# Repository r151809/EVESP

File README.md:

# EVESP
ESP32 (Lolin32) based EV charge controller
Implement charging controller according to SAE J1772 (https://en.wikipedia.org/wiki/SAE_J1772) and relay driver.

Project maturity: just schematics (no testing nor SW yet)!

Only fixed cables are supported (no PP support).

Recidual current (AC+DC) protection is planned with https://deltrixchargers.com/wp-content/uploads/2019/10/WA-DS-015-RCM14-03-Rev-B.pdf
https://www.stegen.com/nl/ev-producten/126-residual-current-sensor.html

Three relays, one for each phase. This is inteded for cases when there is unsymmetrical load in the house, and you still want to charge the car (maybe there is another car charging in one phase already). Another usecase is cars that go to sleep when not charged, and while sleeping they do not accept pre heat commands from the cloud. My take for that would be charging with single phase with 6A current, instead of not charging at all, full 3-phase charging only when you really want to charge. Changing the phases on the fly might not be supported by cars, but that is easy to overcome by stopping the charge before switching on/off any phases.

Misc features:
4 local LEDs
8 IO for external LEDs or buttons
1 up to 12 V LED output for lighting up the charging cable dummy socket (where you keep the cable when it's not connected to car)  

Many ideas (component selection) of the schematic are taken from https://github.com/SmartEVSE/smartevse and from http://www.analogevse.xyz/AnalogEVSE-en.html. 

PWM generation and Wifi connectivity is handled with LoLin32-board:
https://wiki.wemos.cc/products:lolin32:lolin32
It's discontinued already, but you can still find them from ebay.
Pinout is here: https://arduino-projekte.info/wemos-lolin32/

Security:
SW cannot enable relay drivers unless RCM is happy and CP is connected to some load. So the design should be safe in case of forced disconnect and any ground leakage.

Manufacturing of the first PCB patch was done by Itead.cc with files in EVESP.zip.

## Copying
Feel free to copy anything I have added to this project. If it is not too much to ask, please let me know what you are doing (it's not mandatory) :). Also any bug's would be nice to know.

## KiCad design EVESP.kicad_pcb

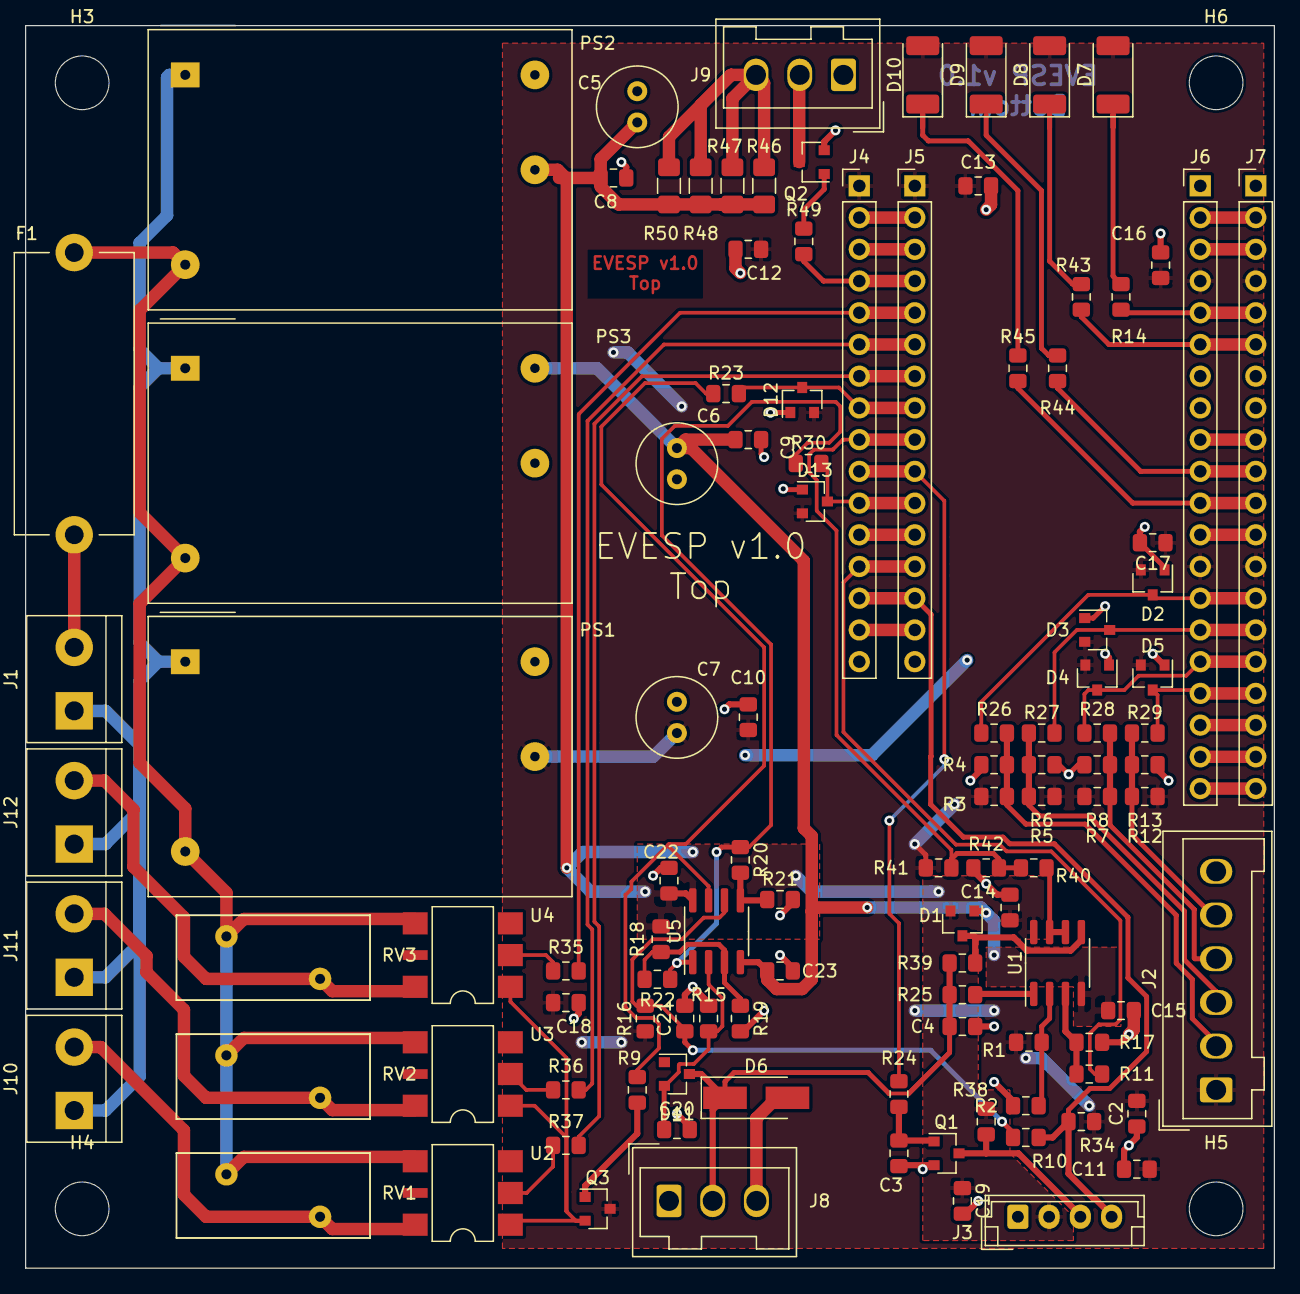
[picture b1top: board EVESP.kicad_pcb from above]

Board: 2 copper layers, 100.0 x 99.5 mm, 113 parts (0 on the bottom side), 68 nets.

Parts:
C2, C12: 10u; C_0805_2012Metric_Pad1.15x1.40mm_HandSolder
C3: DNI 100n; R_0805_2012Metric_Pad1.15x1.40mm_HandSolder
C4: 270p; C_0805_2012Metric_Pad1.15x1.40mm_HandSolder
C5, C6, C7: 47u; C_Radial_D6.3mm_H11.0mm_P2.50mm
C8, C9, C10, C11, C13, C14, C15, C16, C17, C18, C19, C20, C21, C22, C23: 100n; C_0805_2012Metric_Pad1.15x1.40mm_HandSolder
D1, D2, D3, D4, D5, D11, D12, D13: BAT54S; SOT-23
D6: SMAJ13CA-13-F; D_SMA_Handsoldering
D7, D8, D9, D10: LED; LED_2010_5025Metric_Pad1.52x2.65mm_HandSolder
F1: 1.25A; Fuseholder_Cylinder-5x20mm_Stelvio-Kontek_PTF78_Horizontal_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
H3, H4, H5, H6: MountingHole; MountingHole_4.3mm_M4
J1, J10, J11, J12: Screw_Terminal_01x02; TerminalBlock_bornier-2_P5.08mm
J2: Screw_Terminal_01x06; Wago_734-136_1x06_P3.50mm_Vertical
J3: Conn_01x04; JST_EH_B4B-EH-A_1x04_P2.50mm_Vertical
J4: Conn_01x16_Male; PinHeader_1x16_P2.54mm_Vertical
J5: Conn_01x16_Female; PinHeader_1x16_P2.54mm_Vertical
J6: Conn_01x20_Female; PinHeader_1x20_P2.54mm_Vertical
J7: Conn_01x20_Male; PinHeader_1x20_P2.54mm_Vertical
J8, J9: Screw_Terminal_01x03; Wago_734-133_1x03_P3.50mm_Vertical
PS1: IRM-02-3.3; Converter_ACDC_MeanWell_IRM-02-xx_THT
PS2, PS3: IRM-02-12; Converter_ACDC_MeanWell_IRM-02-xx_THT
Q1, Q2, Q3: BC847; SOT-23
R1, R2, R3, R4, R5, R6, R7, R8, R9, R10, R11, R12, R13, R16, R19, R20, R24, R34, R38, R39, R41, R42, R49: 10k; R_0805_2012Metric_Pad1.15x1.40mm_HandSolder
R14, R25, R43, R44, R45: 1k; R_0805_2012Metric_Pad1.15x1.40mm_HandSolder
R15, R22: 1M; R_0805_2012Metric_Pad1.15x1.40mm_HandSolder
R17, R23, R30: 100k; R_0805_2012Metric_Pad1.15x1.40mm_HandSolder
R18: 6k8; R_0805_2012Metric_Pad1.15x1.40mm_HandSolder
R21, R40: 47k; R_0805_2012Metric_Pad1.15x1.40mm_HandSolder
R26, R27, R28, R29, R35, R36, R37: 470R; R_0805_2012Metric_Pad1.15x1.40mm_HandSolder
R46, R47, R48, R50: 470R; R_1206_3216Metric_Pad1.42x1.75mm_HandSolder
RV1, RV2, RV3: V275LA20AP; RV_Disc_D15.5mm_W6.8mm_P7.5mm
U1, U5: LM7332; SOIC-8_3.9x4.9mm_P1.27mm
U2, U3, U4: MOC3063M; SMDIP-6_W7.62mm

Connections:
+3V3: C2.2, C7.1, C10.1, C11.1, C12.1, C13.1, C16.1, C17.1, C18.1, D2.2, D3.2, D4.2, D5.2, D7.2, D8.2, D9.2, D10.2, D12.2, D13.2, J2.1, J4.1, J5.1, J6.4, J6.13, J7.4, J7.13, PS1.4, Q3.3, R1.2, R3.1, R5.1, R7.1, R12.1, R16.1, R34.1, R41.1
+12V: C5.1, C8.1, C14.1, C19.1, C22.1, D1.2, J3.2, PS2.4, R18.1, R38.1, R46.1, R47.1, R48.1, R50.1, U1.8, U5.8
-12V: C6.2, C9.2, C15.2, C23.2, D1.1, PS3.3, U1.4, U5.4
/CP: C4.1, D6.1, D11.3, J8.2, R25.1, R39.2
/CP_in: J4.9, J5.9, R40.1, R41.2, R42.1
/CP_out: J4.13, J5.13, R11.2
/Charge: R20.1, R22.1, R30.1, U5.1
/D0: D2.3, J6.14, J7.14, R26.2
/D1: D3.3, J6.15, J7.15, R27.2
/D2: D4.3, J6.16, J7.16, R28.2
/D3: D5.3, J6.17, J7.17, R29.2
/L1: F1.1, J1.2
/L1_fused: F1.2, PS1.2, PS2.2, PS3.2, RV1.2, RV2.2, RV3.2, U2.4, U3.4, U4.4
/LED0_n: J6.11, J7.11, R45.2
/LED1_n: J6.10, J7.10, R44.2
/LED2_n: J6.6, J7.6, R43.2
/LED3_n: J6.5, J7.5, R14.2
/Light_n: J4.4, J5.4, R49.2
/N: J1.1, J10.1, J11.1, J12.1, PS1.1, PS2.1, PS3.1
/RCM_fail: J3.4, J4.14, J5.14, R10.1, R34.2
/RCM_test: J3.3, Q1.3, R38.2
/RCM_test_n: J4.10, J5.10, R24.1
/REL_0: J10.2, RV1.1, U2.6
/REL_1: J11.2, RV2.1, U3.6
/REL_2: J12.2, RV3.1, U4.6
/Relay_0_n: J4.5, J5.5, R35.2
/Relay_1_n: J4.6, J5.6, R36.2
/Relay_2_n: J4.7, J5.7, R37.2
/SafeToCharge: R9.1, R23.1, U5.7
GND: C2.1, C3.2, C4.2, C5.2, C6.1, C7.2, C8.2, C9.1, C10.2, C11.2, C12.2, C13.2, C14.2, C15.1, C16.2, C17.2, C18.2, C19.2, C20.2, C21.2, C22.2, C23.1, D2.1, D3.1, D4.1, D5.1, D6.2, D12.1, D13.1, J2.6, J3.1, J4.16, J5.16, J6.1, J6.7, J6.8, J6.18, J7.1, J7.7, J7.8, J7.18, J8.1, J8.3, J9.1, PS1.3, PS2.3, PS3.4, Q1.2, Q2.2, R2.1, R4.2, R6.2, R8.2, R13.2, R15.2, R17.1, R19.2, R21.2, R42.2
unnamed: C3.1, Q1.1, R24.2
unnamed: C20.1, D11.2, R15.1, U5.2
unnamed: C21.1, R10.2, R16.2, U5.6
unnamed: D1.3, R39.1, U1.5
unnamed: D7.1, R14.1
unnamed: D8.1, R43.1
unnamed: D9.1, R44.1
unnamed: D10.1, R45.1
unnamed: D12.3, J4.8, J5.8, R23.2
unnamed: D13.3, J4.11, J5.11, R30.2
unnamed: J2.2, R3.2, R4.1, R26.1
unnamed: J2.3, R5.2, R6.1, R27.1
unnamed: J2.4, R7.2, R8.1, R28.1
unnamed: J2.5, R12.2, R13.1, R29.1
unnamed: J4.2, J5.2
unnamed: J4.3, J5.3
unnamed: J4.12, J5.12
unnamed: J4.15, J5.15
unnamed: J6.2, J7.2
unnamed: J6.3, J7.3
unnamed: J6.9, J7.9
unnamed: J6.12, J7.12
unnamed: J6.19, J7.19
unnamed: J6.20, J7.20
unnamed: J9.2, Q2.3
unnamed: J9.3, R46.2, R47.2, R48.2, R50.2
unnamed: Q2.1, R49.1
unnamed: Q3.1, R9.2
unnamed: Q3.2, U2.1, U3.1, U4.1
unnamed: R1.1, R2.2, U1.2
unnamed: R11.1, R17.2, U1.3
unnamed: R18.2, R19.1, R22.2, U5.3
unnamed: R20.2, R21.1, U5.5
unnamed: R25.2, U1.1
unnamed: R35.1, U4.2
unnamed: R36.1, U3.2
unnamed: R37.1, U2.2
unnamed: R40.2, U1.6, U1.7

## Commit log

2020-02-27 Initial version.
2020-02-27 Added PDF of the schematics.
2020-02-27 Update README.md
    Wrote initial info.
2020-02-29 Only 4 external LEDs. Smaller layout.
2020-02-29 Added analog protection against disconnect and diode failure on car side.
2020-02-29 pdf plot
2020-03-01 Added HW safety. No relay drive unless the CP is connected and RCM is happy.
2020-03-01 +12V connectivity fixed
2020-03-01 Layout shrink to <= 10cm x 10 cm
2020-03-01 Added edge prints. Added prints.
2020-03-01 Better +3V3 plane.
2020-03-01 Minor changes.
2020-03-01 PDF update.
2020-03-01 AC side changed for 2mm clearance.
2020-03-01 Added hysteresis to charge -signal. Schematic review changes fixed.
2020-03-01 Layout ready. PDF updated.
2020-03-01 Added gerber and drill files.
2020-03-02 Fixed +-12V drive towards the ESP32 (added resistor and a diode).
2020-03-02 Gerbers generated: Fixed +-12V drive towards the ESP32 (added resistor and a diode).
2020-03-02 Added single drill file with PTH's and NPTH's
2020-03-02 Board cutting fine tuned to leave more clearance on right side connector before edge cut.. Added final production files as zip.
2020-03-12 C2 decal name fixed (both work fine so just a style fix)
2020-03-12 C19-21 decal name fixed (both work fine so just a style fix)
2020-03-14 Capacitors now all use capacitor decal (some were using resistor decal).
2020-03-14 CSV version of BOM.
2021-01-01 PCB's done.
2021-01-01 Fixed the first bug: reistor division in charge -net was inverted.
